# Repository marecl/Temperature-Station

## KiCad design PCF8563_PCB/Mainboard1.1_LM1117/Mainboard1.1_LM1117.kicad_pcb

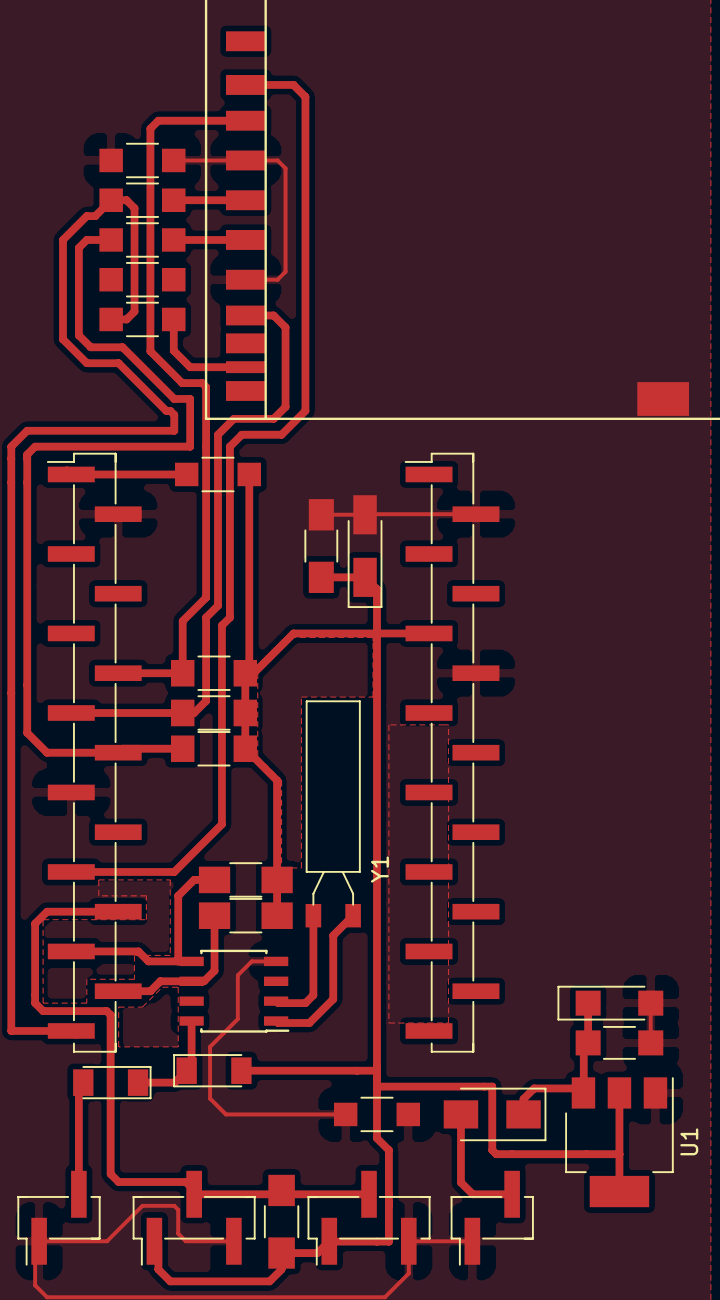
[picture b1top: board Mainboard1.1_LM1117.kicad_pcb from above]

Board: 2 copper layers, 30 parts (0 on the bottom side), 18 nets.

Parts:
C1, C3: 10nF; C_1206_HandSoldering
C2, C4: 10uF; CP_Tantalum_Case-A_EIA-3216-18_Hand
D1, D3: 1N4148; D_MiniMELF
D2: 1N4007; D_SMA
J1, J5: CONN_01X03; Pin_Header_Straight_1x03_Pitch2.54mm_SMD_Pin1Left
J2, J3: CONN_01X15; Pin_Header_Straight_1x15_Pitch2.54mm_SMD_Pin1Left
J4: SD_Card; SDCARD-STANDARD
J6, J7: CONN_01X02; Pin_Header_Straight_1x02_Pitch2.54mm_SMD_Pin1Left
R1, R2, R3, R4: 10k; R_1206_HandSoldering
R5, R6, R7: 4k7; R_1206_HandSoldering
RJ1, RJ2, RJ3, RJ4, RJ5, RJ6: 0; R_1206_HandSoldering
U1: LM1117-3.3; SOT-223-3Lead_TabPin2
U2: PCF8563; SOIC-8_3.9x4.9mm_Pitch1.27mm
Y1: Crystal; Crystal_AT310_d3.0mm_l10.0mm_Horizontal

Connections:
1wire: J1.2, J2.12, J5.2, R5.2
3V3: C3.1, C4.1, D1.2, J1.1, J2.1, J3.5, J4.4, J5.1, R1.1, R2.1, R3.1, R4.1, R5.1, R6.1, R7.1, RJ2.1, RJ2.2, RJ3.1, RJ3.2, U1.2
CS: J2.11, J4.1
GND: C1.2, C2.2, C3.2, C4.2, J1.3, J2.2, J2.9, J3.2, J3.6, J4.3, J4.6, J4.12, J5.3, J6.1, J7.1, RJ4.1, RJ4.2, RJ6.1, RJ6.2, U1.1, U2.4
MISO: J2.7, J4.7, R2.2
MOSI: J2.6, J4.2, R1.2
unnamed: C1.1, C2.1, D2.1, U1.3
unnamed: D1.1, D3.1, U2.8
unnamed: D2.2, J7.2
unnamed: D3.2, J6.2
unnamed: J2.8, R3.2, RJ1.1
unnamed: J4.10, RJ5.2
unnamed: U2.1, Y1.1
unnamed: U2.2, Y1.2
SCK: J4.5, RJ1.2
SCL: J2.14, R7.2, U2.6
SDA: J2.13, R6.2, U2.5
SD_D: J2.15, R4.2, RJ5.1

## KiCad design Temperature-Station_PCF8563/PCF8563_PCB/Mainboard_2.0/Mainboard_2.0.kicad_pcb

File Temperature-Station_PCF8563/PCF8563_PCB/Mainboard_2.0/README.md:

ESP-12E/F as main chip  
No NodeMCU.
One sided.
Not tested.

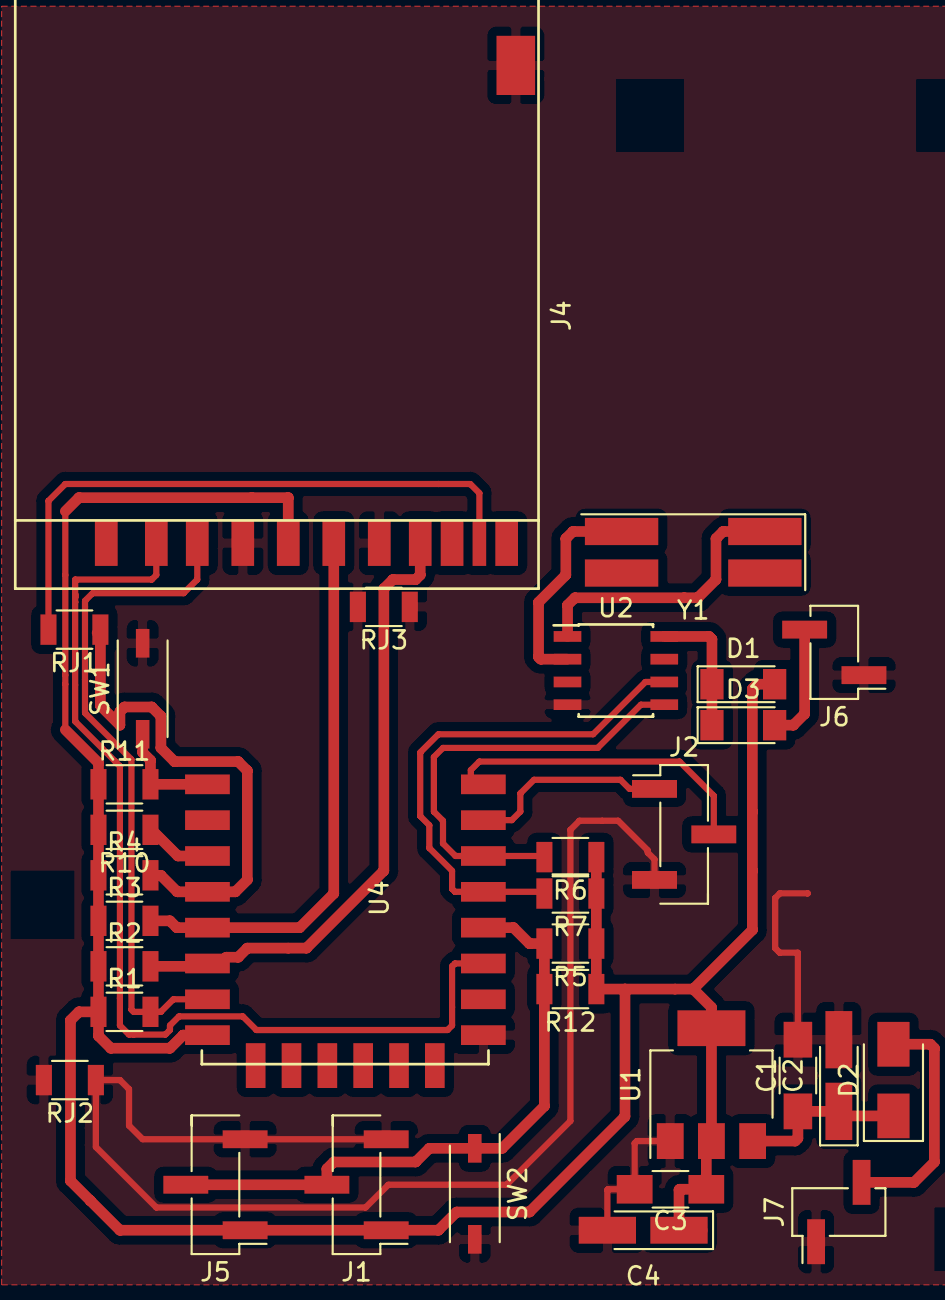
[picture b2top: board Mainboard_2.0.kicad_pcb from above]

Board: 2 copper layers, 32 parts (0 on the bottom side), 21 nets.

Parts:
C1, C3: 10nF; C_1206_HandSoldering
C2, C4: 10uF; CP_Tantalum_Case-A_EIA-3216-18_Hand
D1, D3: 1N4148; D_MiniMELF
D2: 1N4007; D_SMA
J1, J2, J5: CONN_01X03; Pin_Header_Straight_1x03_Pitch2.54mm_SMD_Pin1Left
J4: SD_Card; SDCARD-STANDARD
J6, J7: CONN_01X02; Pin_Header_Straight_1x02_Pitch2.54mm_SMD_Pin1Left
R1, R2, R3, R4: 10k; R_1206
R5, R6, R7: 4k7; R_1206
R10, R11, R12: 1k; R_1206
RJ1, RJ2, RJ3: 0; R_1206
SW1: RESET; SW_DIP_x1_W5.08mm_Slide_Copal_CHS-A
SW2: FLASH; SW_DIP_x1_W5.08mm_Slide_Copal_CHS-A
U1: LM1117-3.3; SOT-223-3Lead_TabPin2
U2: PCF8563; SOIC-8_3.9x4.9mm_Pitch1.27mm
U4: ESP-12E; ESP-12E_SMD
Y1: Crystal; Crystal_SMD_SeikoEpson_MC406-4pin_9.6x4.1mm

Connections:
1wire: J1.2, J5.2, R5.2, R12.2, SW2.1, U4.12
3V3: C3.1, C4.1, D1.2, J1.1, J4.4, J5.1, R1.1, R2.1, R3.1, R4.1, R5.1, R6.1, R7.1, R10.2, R11.1, R12.1, U1.2, U4.8
CS: J4.1, U4.11
GND: C1.2, C2.2, C3.2, C4.2, J1.3, J2.3, J4.3, J4.6, J4.12, J5.3, J6.1, J7.1, RJ2.1, RJ2.2, RJ3.1, RJ3.2, SW1.2, SW2.2, U1.1, U2.4, U4.9
GPIO4: R7.2, U2.6, U4.13
GPIO5: R6.2, U2.5, U4.14
GPIO12: J4.7, R2.2, U4.6
GPIO13: J4.2, R1.2, U4.7
GPIO14: J4.5, R3.2, U4.5
unnamed: C1.1, C2.1, D2.1, U1.3
unnamed: D1.1, D3.1, U2.8
unnamed: D2.2, J7.2
unnamed: D3.2, J6.2
unnamed: J4.10, RJ1.2
unnamed: R10.1, U4.3
unnamed: U2.1, Y1.1
unnamed: U2.2, Y1.2
RESET: R11.2, SW1.1, U4.1
Rx: J2.1, U4.15
SD_D: R4.2, RJ1.1, U4.4
Tx: J2.2, U4.16
